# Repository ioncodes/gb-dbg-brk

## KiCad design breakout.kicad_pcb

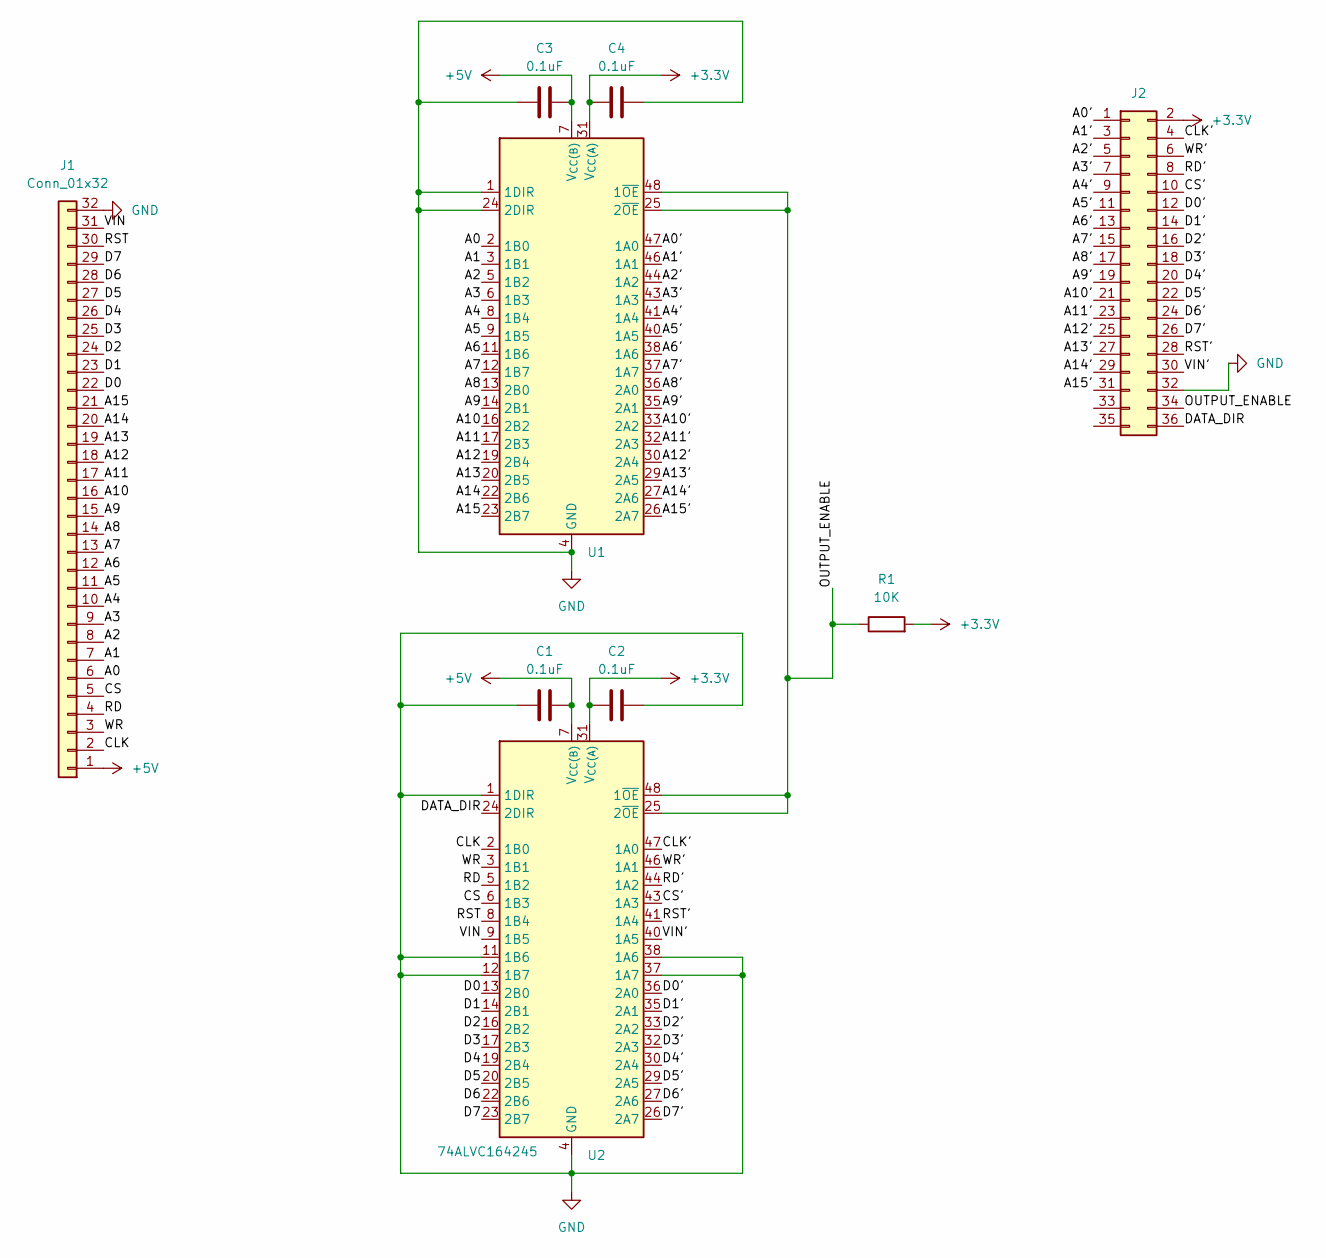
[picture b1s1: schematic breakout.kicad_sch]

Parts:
C1, C2, C3, C4: 0.1uF; C_0805_2012Metric_Pad1.18x1.45mm_HandSolder
J1: Conn_01x32; Base PCB
J2: Conn_02x16_Top_Bottom; PinHeader_2x18_P2.54mm_Vertical_SMD
R1: 10K; R_0805_2012Metric_Pad1.20x1.40mm_HandSolder
U1, U2: 74ALVC164245; TSSOP-48_6.1x12.5mm_P0.5mm

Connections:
+3.3V: C2.1, C4.1, J2.2, R1.2, U1.31 (V_{CC(A)}), U1.42 (V_{CC(A)}), U2.31 (V_{CC(A)}), U2.42 (V_{CC(A)})
+5V: C1.2, C3.2, J1.1, U1.7 (V_{CC(B)}), U1.18 (V_{CC(B)}), U2.7 (V_{CC(B)}), U2.18 (V_{CC(B)})
/A0: J1.6, U1.2 (1B0)
/A0': J2.1, U1.47 (1A0)
/A1: J1.7, U1.3 (1B1)
/A1': J2.3, U1.46 (1A1)
/A2: J1.8, U1.5 (1B2)
/A2': J2.5, U1.44 (1A2)
/A3: J1.9, U1.6 (1B3)
/A3': J2.7, U1.43 (1A3)
/A4: J1.10, U1.8 (1B4)
/A4': J2.9, U1.41 (1A4)
/A5: J1.11, U1.9 (1B5)
/A5': J2.11, U1.40 (1A5)
/A6: J1.12, U1.11 (1B6)
/A6': J2.13, U1.38 (1A6)
/A7: J1.13, U1.12 (1B7)
/A7': J2.15, U1.37 (1A7)
/A8: J1.14, U1.13 (2B0)
/A8': J2.17, U1.36 (2A0)
/A9: J1.15, U1.14 (2B1)
/A9': J2.19, U1.35 (2A1)
/A10: J1.16, U1.16 (2B2)
/A10': J2.21, U1.33 (2A2)
/A11: J1.17, U1.17 (2B3)
/A11': J2.23, U1.32 (2A3)
/A12: J1.18, U1.19 (2B4)
/A12': J2.25, U1.30 (2A4)
/A13: J1.19, U1.20 (2B5)
/A13': J2.27, U1.29 (2A5)
/A14: J1.20, U1.22 (2B6)
/A14': J2.29, U1.27 (2A6)
/A15: J1.21, U1.23 (2B7)
/A15': J2.31, U1.26 (2A7)
/CLK: J1.2, U2.2 (1B0)
/CLK': J2.4, U2.47 (1A0)
/CS: J1.5, U2.6 (1B3)
/CS': J2.10, U2.43 (1A3)
/D0: J1.22, U2.13 (2B0)
/D0': J2.12, U2.36 (2A0)
/D1: J1.23, U2.14 (2B1)
/D1': J2.14, U2.35 (2A1)
/D2: J1.24, U2.16 (2B2)
/D2': J2.16, U2.33 (2A2)
/D3: J1.25, U2.17 (2B3)
/D3': J2.18, U2.32 (2A3)
/D4: J1.26, U2.19 (2B4)
/D4': J2.20, U2.30 (2A4)
/D5: J1.27, U2.20 (2B5)
/D5': J2.22, U2.29 (2A5)
/D6: J1.28, U2.22 (2B6)
/D6': J2.24, U2.27 (2A6)
/D7: J1.29, U2.23 (2B7)
/D7': J2.26, U2.26 (2A7)
/DATA_DIR: J2.36, U2.24 (2DIR)
/OUTPUT_ENABLE: J2.34, R1.1, U1.25 (2~OE), U1.48 (1~OE), U2.25 (2~OE), U2.48 (1~OE)
/RD: J1.4, U2.5 (1B2)
/RD': J2.8, U2.44 (1A2)
/RST: J1.30, U2.8 (1B4)
/RST': J2.28, U2.41 (1A4)
/VIN: J1.31, U2.9 (1B5)
/VIN': J2.30, U2.40 (1A5)
/WR: J1.3, U2.3 (1B1)
/WR': J2.6, U2.46 (1A1)
GND: C1.1, C2.2, C3.1, C4.2, J1.32, J2.32, U1.1 (1DIR), U1.4 (GND), U1.10 (GND), U1.15 (GND), U1.21 (GND), U1.24 (2DIR), U1.28 (GND), U1.34 (GND), U1.39 (GND), U1.45 (GND), U2.1 (1DIR), U2.4 (GND), U2.10 (GND), U2.11 (1B6), U2.12 (1B7), U2.15 (GND), U2.21 (GND), U2.28 (GND), U2.34 (GND), U2.37 (1A7), U2.38 (1A6), U2.39 (GND), U2.45 (GND)

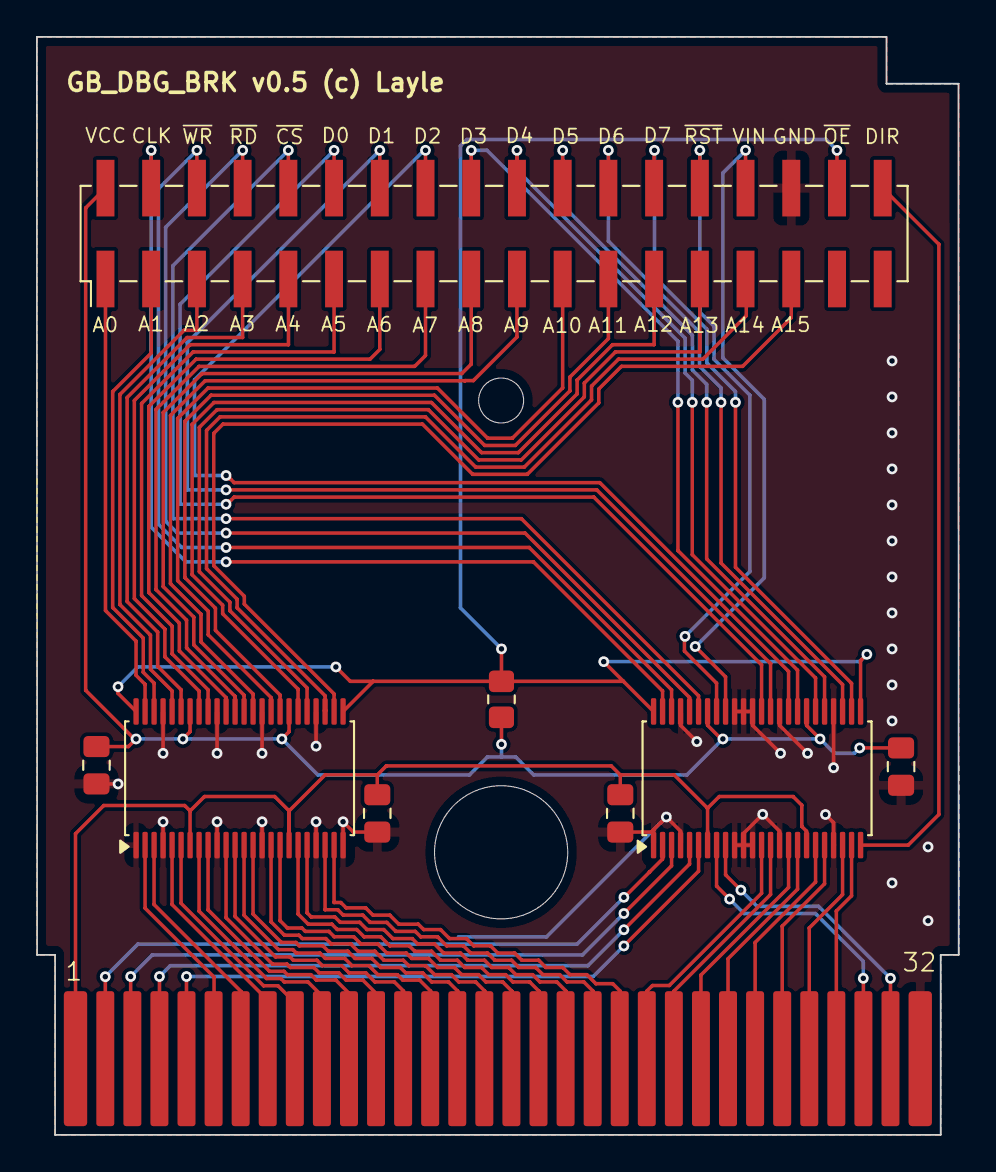
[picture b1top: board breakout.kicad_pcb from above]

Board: 2 copper layers, 51.2 x 61.0 mm, 9 parts (0 on the bottom side), 65 nets.

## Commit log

2025-12-27 init
2025-12-30 thanks to bigbass
